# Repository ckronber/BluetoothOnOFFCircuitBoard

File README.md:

# BluetoothOnOFFCircuitBoard
Circuit board created for turning power on and off to a Bluetooth audio board

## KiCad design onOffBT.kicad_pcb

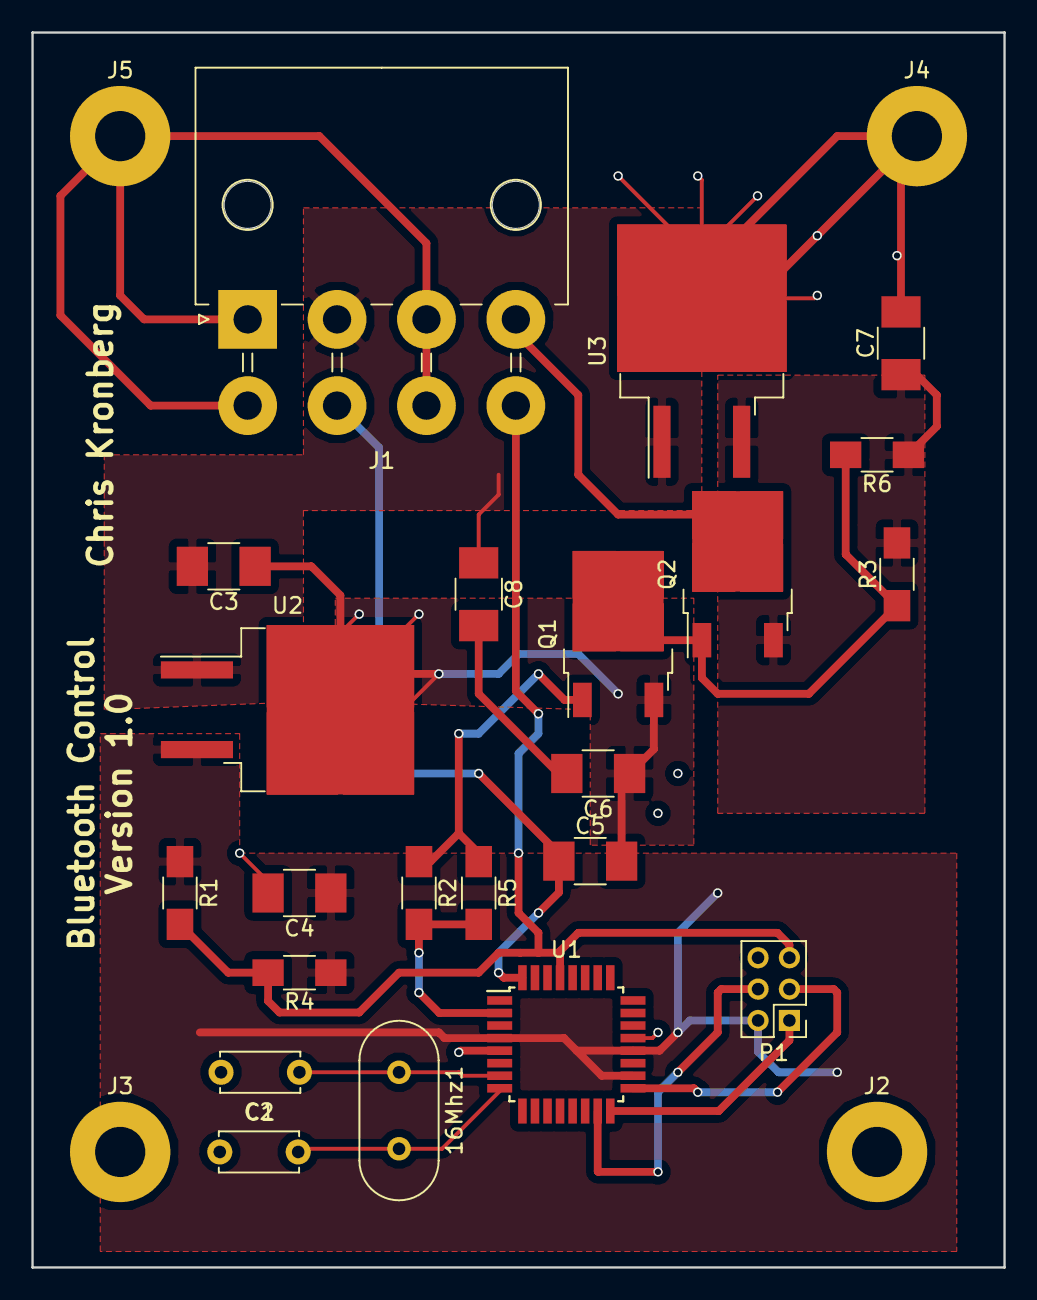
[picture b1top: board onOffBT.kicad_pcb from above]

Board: 2 copper layers, 62.0 x 78.7 mm, 26 parts (0 on the bottom side), 16 nets.

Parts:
16Mhz1: Crystal; Crystal_HC49-4H_Vertical
C1, C2: 22pF; C_Disc_D5.0mm_W2.5mm_P5.00mm
C3, C6: .22uF; C_1210_HandSoldering
C4, C5, C7, C8: .1uF; C_1210_HandSoldering
J1: Molex 2x4; Molex_MegaFit_2x04x5.70mm_Angled
J2, J3, J4, J5: Conn_01x01; MountingHole_3.2mm_M3_Pad
P1: ISCP PINS; Pin_Header_Straight_2x03_Pitch2.00mm
Q1: Q_NMOS_GDS; TO-252-2
Q2: Q_PMOS_GDS; TO-252-2
R1, R2, R3, R4, R5, R6: 20k; R_1206_HandSoldering
U1: ATMEGA328PB-AU; TQFP-32_7x7mm_Pitch0.8mm
U2: L7805; TO-263-2
U3: L7812; TO-263-2

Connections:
12vOut: J1.4, Q2.2
15vIN: C3.2, C8.1, J1.2, U2.1, U3.1
+5V: C4.1, P1.2, R1.1, R4.1, U1.4, U1.18, U1.20, U2.3
+12V: C7.1, Q2.3, R3.2, R6.1, U3.3
ArduinoReset: J1.8, P1.5, R1.2, R4.2, U1.29
Button: C5.1, J1.6, U1.32
GND: C1.2, C2.1, C3.1, C4.2, C5.2, C6.1, C7.2, J1.1, J1.3, J1.5, J1.7, J2.1, J3.1, J4.1, J5.1, P1.6, Q1.3, U1.5, U1.21, U2.2, U3.2
MISO: P1.1, U1.16
MOSI: P1.4, U1.15
unnamed: C6.2, C8.2
unnamed: Q1.1, R2.1, R5.1
unnamed: Q1.2, Q2.1, R3.1, R6.2
PD4: R2.2, R5.2, U1.2
SCK: P1.3, U1.17
XTAL1: 16Mhz1.1, C1.1, U1.7
XTAL2: 16Mhz1.2, C2.2, U1.8
